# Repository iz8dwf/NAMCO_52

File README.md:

# Namco_52_avr
Namco 52xx custom IC replacement

This daughterboard replaces the 52XX custom IC used for example in Pole
Position as speech generator.
It is implemented with a 44 pin ATMega8515 MCU following the reverse 
engineering information found at http://www.whiterocker.com/blog/namco-52xx.html

I've also checked both the Pole Position schematic and 52xx's ROM and the 
Bosconian schematic and its 52xx ROM and of course MAME's implementation, see the info 
subdirectory.
It seems that on Bosconian the 52xx clock arrives on PIN 1 instead of PIN 2 as on 
Pole Position, so in that case, a 0 ohms resistor or jumper must be soldered on CK1
position. ONLY solder one jumper either on CK1 OR CK2.

The MCU can be programmed by connecting the appropriate daughterboard pins 
to the needed SPI pins. I've not added any programming header for laziness/space
reasons, see the images.

WARNING: only tested on Pole Position!!!

If you want to try this replacement on another game contact me first!

USE AT YOUR OWN RISK

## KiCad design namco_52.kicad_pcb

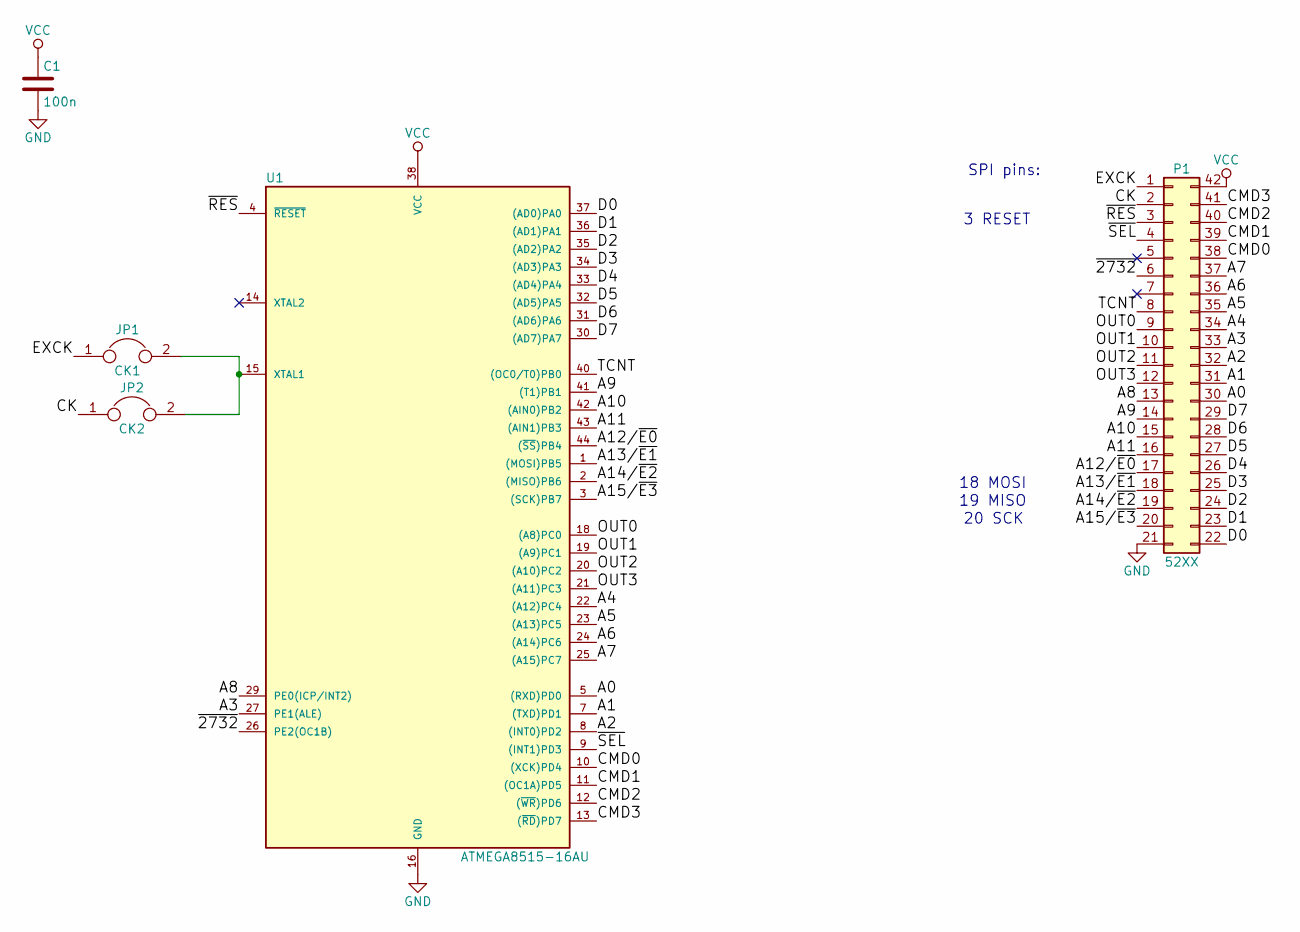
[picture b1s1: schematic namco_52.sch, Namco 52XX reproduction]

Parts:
C1: 100n; C_0805_HandSoldering
JP1: CK1; R_0805_HandSoldering
JP2: CK2; R_0805_HandSoldering
P1: 52XX; DIP-42_W15.24mm
U1: ATMEGA8515-16AU; TQFP-44_10x10mm_Pitch0.8mm

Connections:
/A0: P1.30, U1.5 ((RXD)PD0)
/A1: P1.31, U1.7 ((TXD)PD1)
/A2: P1.32, U1.8 ((INT0)PD2)
/A3: P1.33, U1.27 (PE1(ALE))
/A4: P1.34, U1.22 ((A12)PC4)
/A5: P1.35, U1.23 ((A13)PC5)
/A6: P1.36, U1.24 ((A14)PC6)
/A7: P1.37, U1.25 ((A15)PC7)
/A8: P1.13, U1.29 (PE0(ICP/INT2))
/A9: P1.14, U1.41 ((T1)PB1)
/A10: P1.15, U1.42 ((AIN0)PB2)
/A11: P1.16, U1.43 ((AIN1)PB3)
/A12/~E0: P1.17, U1.44 ((~SS~)PB4)
/A13/~E1: P1.18, U1.1 ((MOSI)PB5)
/A14/~E2: P1.19, U1.2 ((MISO)PB6)
/A15/~E3: P1.20, U1.3 ((SCK)PB7)
/CK: JP2.1, P1.2
/CMD0: P1.38, U1.10 ((XCK)PD4)
/CMD1: P1.39, U1.11 ((OC1A)PD5)
/CMD2: P1.40, U1.12 ((~WR~)PD6)
/CMD3: P1.41, U1.13 ((~RD~)PD7)
/D0: P1.22, U1.37 ((AD0)PA0)
/D1: P1.23, U1.36 ((AD1)PA1)
/D2: P1.24, U1.35 ((AD2)PA2)
/D3: P1.25, U1.34 ((AD3)PA3)
/D4: P1.26, U1.33 ((AD4)PA4)
/D5: P1.27, U1.32 ((AD5)PA5)
/D6: P1.28, U1.31 ((AD6)PA6)
/D7: P1.29, U1.30 ((AD7)PA7)
/EXCK: JP1.1, P1.1
/OUT0: P1.9, U1.18 ((A8)PC0)
/OUT1: P1.10, U1.19 ((A9)PC1)
/OUT2: P1.11, U1.20 ((A10)PC2)
/OUT3: P1.12, U1.21 ((A11)PC3)
/TCNT: P1.8, U1.40 ((OC0/T0)PB0)
/~2732: P1.6, U1.26 (PE2(OC1B))
/~RES: P1.3, U1.4 (~RESET)
/~SEL: P1.4, U1.9 ((INT1)PD3)
GND: C1.2, P1.21, U1.16 (GND)
unnamed: JP1.2, JP2.2, U1.15 (XTAL1)
VCC: C1.1, P1.42, U1.38 (VCC)

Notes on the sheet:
18 MOSI
SPI pins:
19 MISO
20 SCK
3 RESET

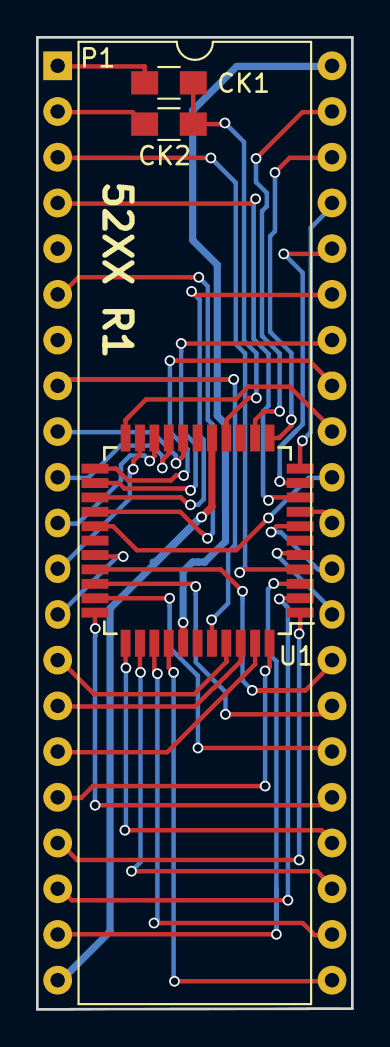
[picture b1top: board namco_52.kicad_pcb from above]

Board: 2 copper layers, 17.5 x 54.0 mm, 5 parts (1 on the bottom side), 41 nets.

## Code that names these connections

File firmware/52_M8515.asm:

; Namco 52XX replacement
; ATMega8515 MCU
; V 1.0
; IZ8DWF 08/2024

.device  ATmega8515

; fuses: CKSEL3..0 = 0000 (external clock)
;        CKOPT = 1, BOOTRST = 1
;        HB 11011001 0xd9
;        LB 11100000 0xe0

; Inputs:
; Port A = byte read from ROM
; Port D7..4 = sample index from CPU (read during INT1)
; PE2 = /2732 read during initialization

; PB0 special  (T0 for external counter clock)
; PD3 special  (INT1)

; Outputs:
; PB1 = A9
; PB2 = A10
; PB3 = A11
; PB4 = A12 if /2732 = 1, /E0 if 0
; PB5 = A13 if /2732 = 1, /E1 if 0
; PB6 = A14 if /2732 = 1, /E2 if 0
; PB7 = A15 if /2732 = 1, /E3 if 0

; PC7..4  = A7..4
; PD2..0  = A2..0
; PE1 = A3
; PE0 = A8

; registers map
; r0 = always 0
; r1 = /2732
; r2 = general purpose
; r3 = playing clip index
; r4 = used in address output routine
; r5 = status register save in interrupts

; r16 = general purpose always lost (DO NOT use in interrupts)
; r17 = clip index read from CPU
; r18 = general purpose (mostly used in ROM address output)
; r19 = current sample
; r20 = timer compare value/interrupt enable mask
; r21 = only used in timer interrupt routine
; r22 = only used in timer interrupt routine

; r24 = sample index

; r26 low, r27 high = X 
; r28 low, r29 high = Y
; r30 low, r31 high = Z

; ATMega8515 I/O space

.equ base = 0x0000
.equ init = 0x0011
.equ ram  = 0x0060
.equ ramend = 0x025f

.equ SREG = 0x3f
.equ SPH = 0x3e
.equ SPL = 0x3d
.equ GICR = 0x3b
.equ GIFR = 0x3a
.equ TIMSK = 0x39
.equ TIFR = 0x38
.equ SPMCR = 0x37
.equ EMCUCR = 0x36
.equ MCUCR = 0x35
.equ MCUCSR = 0x34
.equ TCCR0 = 0x33
.equ TCNT0 = 0x32
.equ OCR0 = 0x31
.equ SFIOR = 0x30
.equ TCCR1A = 0x2f
.equ TCCR1B = 0x2e
.equ TCNT1H = 0x2d
.equ TCNT1L = 0x2c
.equ OCR1AH = 0x2b
.equ OCR1AL = 0x2a
.equ OCR1BH = 0x29
.equ OCR1BL = 0x28
.equ ICR1H = 0x25
.equ ICR1L = 0x24
.equ WDTCR = 0x21
.equ UBRRH = 0x20
.equ UCSRC = 0x20
.equ EEARH = 0x1f
.equ EEARL = 0x1e
.equ EEDR = 0x1d
.equ EECR = 0x1c
.equ PORTA = 0x1b
.equ DDRA = 0x1a
.equ PINA = 0x19
.equ PORTB = 0x18
.equ DDRB = 0x17
.equ PINB = 0x16
.equ PORTC = 0x15
.equ DDRC = 0x14
.equ PINC = 0x13
.equ PORTD = 0x12
.equ DDRD = 0x11
.equ PIND = 0x10
.equ SPDR = 0x0f
.equ SPSR = 0x0e
.equ SPCR = 0x0d
.equ UDR = 0x0c
.equ UCSRA = 0x0b
.equ UCSRB = 0x0a
.equ UBRRL = 0x09
.equ ACSR = 0x08
.equ PORTE = 0x07
.equ DDRE = 0x06
.equ PINE = 0x05
.equ OSCCAL = 0x04


; ram/local constants 
; timer compare value on Pole Position should result in approx. 4 kHz sample
; reproduction rate.
.equ INTMAX	= 0x30	; internal timer compare (top) value

; timer compare value when using external clock. Assuming it's 1 cycle = 
; 1 sample. I've never seen an actual board using external clock so far
.equ EXTMAX	= 0x01	; external timer compare (top)  value

.cseg
.org base
	rjmp RESET
	rjmp DUMMYI	; external interrupt 0
	rjmp INT1	; external interrupt 1
	rjmp DUMMYI	; timer 1 capture
	rjmp DUMMYI	; timer 1 compare A
	rjmp DUMMYI	; timer 1 compare B
	rjmp DUMMYI	; timer 1 overflow 
	rjmp DUMMYI	; timer 0 overflow 
	rjmp DUMMYI	; SPI serial xfer complete 
	rjmp DUMMYI	; uart rxc
	rjmp DUMMYI	; uart udre
	rjmp DUMMYI	; uart txc
	rjmp DUMMYI	; analog comp
	rjmp DUMMYI	; external interrupt 2
	rjmp TMI	; timer 0 compare
	rjmp DUMMYI	; eeprom ready
	rjmp DUMMYI	; store program memory ready
	
.org init


INT1:
	in r17, PIND	; read sample clip index 
	in r5, SREG	; save status register
	andi r17, 0xf0  ; data is on high nibble only
	swap r17	; so put it on low nibble now
	out SREG, r5	; restore status
DUMMYI:	reti

TMI:
	in r5, SREG	; save status register
	in r21, PORTC
	andi r21, 0xf0
	mov r22, r19
	andi r22, 0x0f
	or r22, r21
	out PORTC, r22
	swap r19
	inc r24		; increment played sample index
	out SREG, r5	; restore status
	reti

RESET:	cli
	sbi ACSR, 7		; power off analog comparator
	clr r0
	clr r17			; clear sample index register
	out DDRA, r17		; port A is all inputs
	out PORTA, r17		; also disable pullups

	ldi r16, low(ramend)	; set stack pointer (low byte)
	out SPL, r16
	ldi r16, high(ramend)	; high byte now
	out SPH, r16

	ldi r16, 0xfe		
	out DDRB, r16		; PB1 to PB7 are outputs
	ldi r16, 0xff		
	out DDRC, r16		; PC0 to PC7 are outputs
	ldi r16, 0x07		
	out DDRD, r16		; PD0 to PD2  are outputs
	ldi r16, 0x03		
	out DDRE, r16		; PE0 and PE1 are outputs	
	cbi PORTE, 2		; disable pullup on PE2 input
	clr r1
	sbic PINE, 2		; check /2732 pin
	inc r1
	clr r27			; check configuration byte at ROM addr 0x0020
	ldi r26, 0x20
	rcall romrd
	in r18, PINA
	ldi r20, INTMAX		; set the timer top value
	ldi r16, 0x0a		; CTC, internal clock prescaler = 1/8
	cpi r18, 0xf0		; internal timer = 0xf0, external = 0xff
	breq timinit 
	ldi r20, EXTMAX
	ldi r16, 0x0f		; CTC, external clock rising edge
timinit:
	out OCR0, r20
	out TCCR0, r16
	ldi r20, 0x01		; timer interrupt on compare match
	
	in r16, MCUCR		; setup INT1 as falling edge
	ori r16, 0x08
	out MCUCR, r16
	in r16, GICR
	ori r16, 0x80		; enable INT1
	out GICR, r16
	sei			; enable interrupts

main:
	tst r17 		; waits for a clip index
	breq main		; (no clip playing if looping here)

clip:	rcall getadd		; get start/stop addresses of the clip to play
	clr r24			; clear sample index
	rcall rsamp		; get first sample pair in r19
	mov r3, r17	
	out TCNT0, r0		; timer is running, so reset its value
	out TIFR, r20		; then clear the interrupt flag 
	out TIMSK, r20		; then enable timer 0 OC interrupt
waitpl:	cpi r24, 0x02		; wait for current samples to be played
	brlo waitpl

	cp r29, r31		; check if we are at the end of the samples
	brne nextrd
	cp r28, r30
	brne nextrd
	out TIMSK, r0		; end: disable all timer 0/1 interrupts
	clr r17
	rjmp main

nextrd:	cp r3, r17		; see if we got a higher clip to play
	brlo clip		; yes, start the new one
	adiw r28, 0x01		; otherwise increment sample address
	rcall rsamp		; read a new sample pair in r19
	clr r24	
	rjmp waitpl

; subroutines


rsamp:	movw r26, r28
	rcall romrd
	in r19, PINA
	ret

getadd:				; gets start (Y) and stop (Z) addresses
				; of the clip index in r17
	clr r26
	clr r27
	add r26, r17		; low clip end address at 0x0000 + clip
	rcall romrd		
	in r30, PINA
	dec r26			; low clip start address at 0x0000 + clip - 1
	rcall romrd
	in r28, PINA		
	adiw r26, 0x10		; high clip start address at 0x0010 + clip - 1
	rcall romrd
	in r29, PINA
	inc r26			; high clip end address at 0x0010 + clip
	rcall romrd		
	in r31, PINA
	ret

romrd:				; gets the 16 bit address on r27,r26 and
				; sets the address lines for ROM access
				; needs in rXX, PINA after the call
	out PORTE, r0		; clears A3, A8
	mov r18, r26
	andi r18, 0x07		; lowest three addresses go on PORTD
	out PORTD, r18
	mov r18, r26
	andi r18, 0xf0		; A4 to A7 on PORTC	
	in r16, PORTC		
	andi r16, 0x0f
	or r16, r18
	out PORTC, r16
	sbrc r26, 3
	sbi PORTE, 1		; sets A3
	sbrc r27, 0
	sbi PORTE, 0		; sets A8
	
	ldi r16, 0xfe
	mov r18, r27 		
	tst r1			; check if 2732 mode
	brne haddr		; no, set all higher Axx

	andi r18, 0x30		; 2732 mode, need to assert one enable line
	swap r18
	clr r4
	sec
lop1:	rol r4
	tst r18
	breq end32
	dec r18
	rjmp lop1
end32:	swap r4
	eor r16, r4
	mov r18, r27
	ori r18, 0xf0
haddr:  and r18, r16
	out PORTB, r18
	ret			

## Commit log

2024-09-04 Initial release
2024-09-04 Added images
